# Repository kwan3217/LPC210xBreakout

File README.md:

# LPC210xBreakout
Breakout board for NXP LPC2101/2/3 microcontroller. The pinout for the crystals and power is similar enough to that of an LPC2104/5/6 that it will
probably work for that chip as well.

# How to use
All 48 pins on the chip are broken out to their respective pins on the board. Digital grounds (3 pins) are connected together. Several pins are connected to each other through default-shorted jumpers. If you wish, you can cut the jumpers with a razor blade.

 * Analog ground (pin 31) to digital ground
 * Analog power (pin 42) to digital I/O (3.3V) power
 * RTC power (pin 4) to digital I/O (3.3V) power

The chip uses a 1.8V core voltage, and needs both 3.3V and 1.8V to operate. I have included a 3.3->1.8V regulator on the board. Since the 1.8V supply pin is broken out, you don't have to use this regulator if you don't want -- just don't populate the regulator.

# Interesting things and oddities
The board file has the footprint for a TSSOP-16 and a TSSOP-20 chip. These footprints are outside of the board outline, and are there so that the stencil
I make also has those footprints, for another project I am working on.

# Getting this board
I recommend getting the board from https://oshpark.com/shared_projects/SdR4aknh. There isn't an explicit bill of materials. Instead, the bill of materials is encoded in the schematic (.kicad_sch) file. Each component has either a Digikey or Mouser part number -- use those for generating your own bill of materials. If those exact parts aren't available (Darn chip shortage!) you are on your own, but those numbers should still lead you to the specifications for the given parts, so you can pick substitutes.

# How to modify
This board is Open Hardware, licensed under the GPL 3.0 license. That's the legal part. My intent is that:
 * You can make as many exact copies of the board as you wish, including with my StKwan logo. The link at oshpark.com is a good place to do that.
 * You may modify the board as you wish, but if you do so, please remove my StKwan logo from the board. If you are modifying it, you should take pride in your work and put your name on it anyway.
   * It's fine if the _only_ modification you make to the board is to put your name on it. Take my logo off in that case, too.
 * Follow the rest of the GPL as concerning share-alike, etc.
 * The only reason I am licensing the board at all is so I can put the OSHW logo on the board.

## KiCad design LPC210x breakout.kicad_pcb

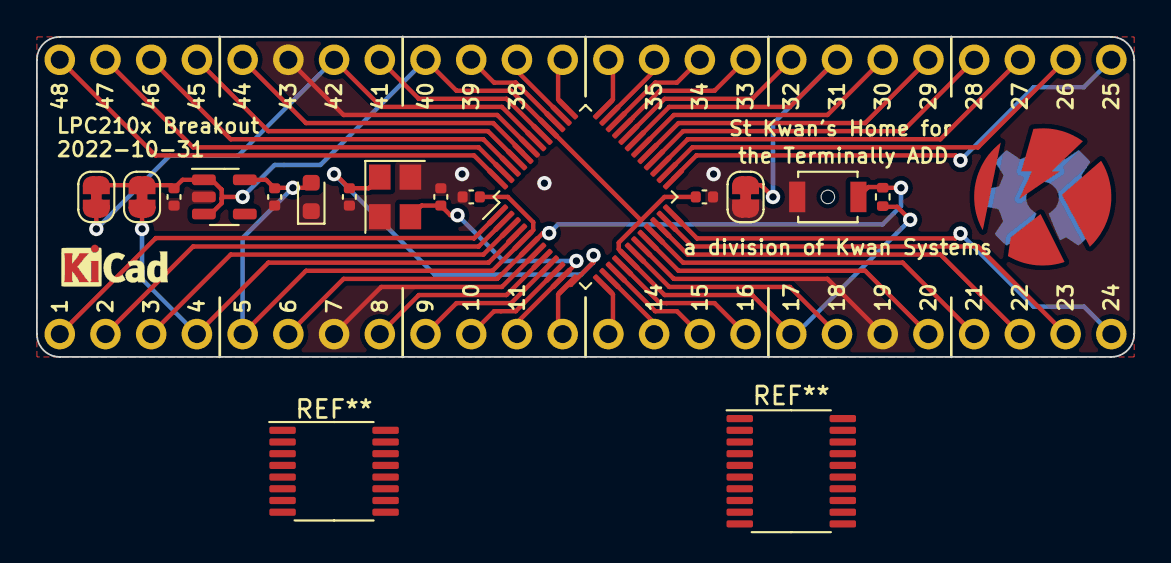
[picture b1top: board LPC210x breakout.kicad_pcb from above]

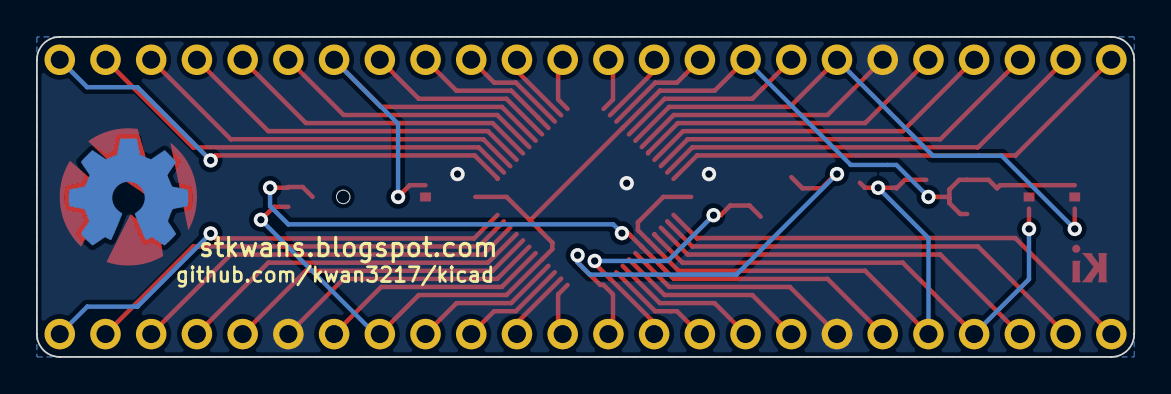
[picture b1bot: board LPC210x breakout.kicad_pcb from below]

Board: 2 copper layers, 61.0 x 17.8 mm, 20 parts (3 on the bottom side), 45 nets.

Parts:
C105, C117, C201, C205: 1uF; C_0402_1005Metric
C111, C112: 22pF; C_0402_1005Metric
D201: RED; LED_0603_1608Metric
G101: KwanSystems; StKwansSoldermask
G102: DesignedWithKicad; Symbol_KiCAD-Logo_CopperAndSilkScreenTop_small
G103: OSHW; OSHW-Symbol_6.7x6mm_SolderMask
J101, J102: Conn_01x24_Male; PinHeader_1x24_P2.54mm_Vertical
JP104: VBAT; SolderJumper-2_P1.3mm_Bridged_RoundedPad1.0x1.5mm
JP131: AnalogGround; SolderJumper-2_P1.3mm_Bridged_RoundedPad1.0x1.5mm
JP142: VDDA; SolderJumper-2_P1.3mm_Bridged_RoundedPad1.0x1.5mm
R106: 10k; R_0402_1005Metric
S106: B3U-1000; SW_SPST_B3U-1000P-B
U101: LPC2103; LQFP-48_7x7mm_P0.5mm
U201: TCR2EF 1.8V; SOT-23-5
Y101: 12MHz; Crystal_SMD_Abracon_ABM8G-4Pin_3.2x2.5mm

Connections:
+1V8: C105.1, C205.1, D201.2 (A), J101.5, U101.5 (VDD(1V8)), U201.5 (OUT)
+3V3: C117.1, C201.1, J101.17, J102.16, JP104.1 (A), JP142.1 (A), R106.2, U101.17 (VDD(3V3)), U101.40 (VDD(3V3)), U201.1 (IN), U201.3 (EN)
/P01: J101.1, U101.1 ((MAT1.2/MISO1)P0.19)
/P02: J101.2, U101.2 ((MAT1.3/MOSI1)P0.20)
/P03: J101.3, U101.3 ((SSEL1/MAT3.0)P0.21)
/P04: J101.4, JP104.2 (B), U101.4 (VBAT)
/P06: J101.6, R106.1, S106.2 (B), U101.6 (~RST)
/P08: J101.8, U101.8 ((~TRST/CAP2.0)P0.27)
/P09: J101.9, U101.9 ((TMS/CAP2.1)P0.28)
/P10: J101.10, U101.10 ((TCK/CAP2.2)P0.29)
/P11: C111.2, J101.11, U101.11 (XTAL1), Y101.3
/P12: C112.2, J101.12, U101.12 (XTAL2), Y101.1
/P13: J101.13, U101.13 ((TXD0/MAT3.1)P0.0)
/P14: J101.14, U101.14 ((RXD0/MAT3.2)P0.1)
/P15: J101.15, U101.15 ((TDI/MAT3.3)P0.30)
/P16: J101.16, U101.16 ((TDO)P0.31)
/P18: J101.18, U101.18 ((SCL0/CAP0.0)P0.2)
/P20: J101.20, U101.20 (RTCX1)
/P21: J101.21, U101.21 ((SDA0/MAT0.0)P0.3)
/P22: J101.22, U101.22 ((SCK0/CAP0.1)P0.4)
/P23: J101.23, U101.23 ((MISO0/MAT0.1)P0.5)
/P24: J101.24, U101.24 ((MOSI0/CAP0.2)P0.6)
/P25: J102.1, U101.25 (RTCX2)
/P26: J102.2, U101.26 (RTCK)
/P27: J102.3, U101.27 (DBGSEL)
/P28: J102.4, U101.28 ((SSEL0/MAT2.0)P0.7)
/P29: J102.5, U101.29 ((TXD1/MAT2.1)P0.8)
/P30: J102.6, U101.30 ((RXD1/MAT2.2)P0.9)
/P32: J102.8, U101.32 ((AD0.0)P0.22)
/P33: J102.9, U101.33 ((AD0.1)P0.23)
/P34: J102.10, U101.34 ((AD0.2)P0.24)
/P35: J102.11, U101.35 ((RTS1/CAP1.0/AD0.3)P0.10)
/P36: J102.12, U101.36 ((CTS1/CAP1.1/AD0.4)P0.11)
/P37: J102.13, U101.37 ((DSR1/MAT1.0/AD0.5)P0.12)
/P38: J102.14, U101.38 ((AD0.6)P0.25)
/P39: J102.15, U101.39 ((AD0.7)P0.26)
/P41: J102.17, U101.41 ((DTR1/MAT1.1)P0.13)
/P42: J102.18, JP142.2 (B), U101.42 (VDDA)
/P44: J102.20, U101.44 ((DCD1/SCK1/EINT1)P0.14)
/P45: J102.21, U101.45 ((RI1/EINT2)P0.15)
/P46: J102.22, U101.46 ((EINT0/MAT0.2)P0.16)
/P47: J102.23, U101.47 ((CAP1.2/SCL1)P0.17)
/P48: J102.24, U101.48 ((CAP1.3/SDA1)P0.18)
GND: C105.2, C111.1, C112.1, C117.2, C201.2, C205.2, D201.1 (K), J101.7, J101.19, J102.19, JP131.1 (A), S106.1 (A), U101.7 (VSS), U101.19 (VSS), U101.43 (VSS), U201.2 (GND), Y101.2, Y101.4
GNDA: J102.7, JP131.2 (B), U101.31 (VSSA)

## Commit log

2022-10-31 Add correct link to oshpark project
